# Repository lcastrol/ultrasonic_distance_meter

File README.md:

# ultrasonic_distance_meter
An ultrasonic distance meter 

============
Dependencies
============

Install GCC for AVR and libraries
```
$ sudo apt-get install gcc-avr binutils-avr avr-libc avrdude
```
GDB for AVR
```
$ sudo apt-get install gdb-avr
```

Install Eclipse and the eclipse C development toolkit

```
apt-get install eclipse eclipse-cdt
```

Install eclipse avr plugin

Go to the Software installation dialog (Help > Install New Software...)

Then enter the updatesite URL http://avr-eclipse.sourceforge.net/updatesite into the "Work with:" field. Select the AVR Eclipse Plugin from the list, hit "Next>" and follow the instructions on the next pages.

AVREclipseInstallUpdatesiteScreenshot.png

===================
Configure Eclipse
===================

Go over Window > Preferences

Click on AVR > AVRDude tab
Click on Add button

Choose Programmer Hardware = Atmel AVR ISP

===================
Usage
===================

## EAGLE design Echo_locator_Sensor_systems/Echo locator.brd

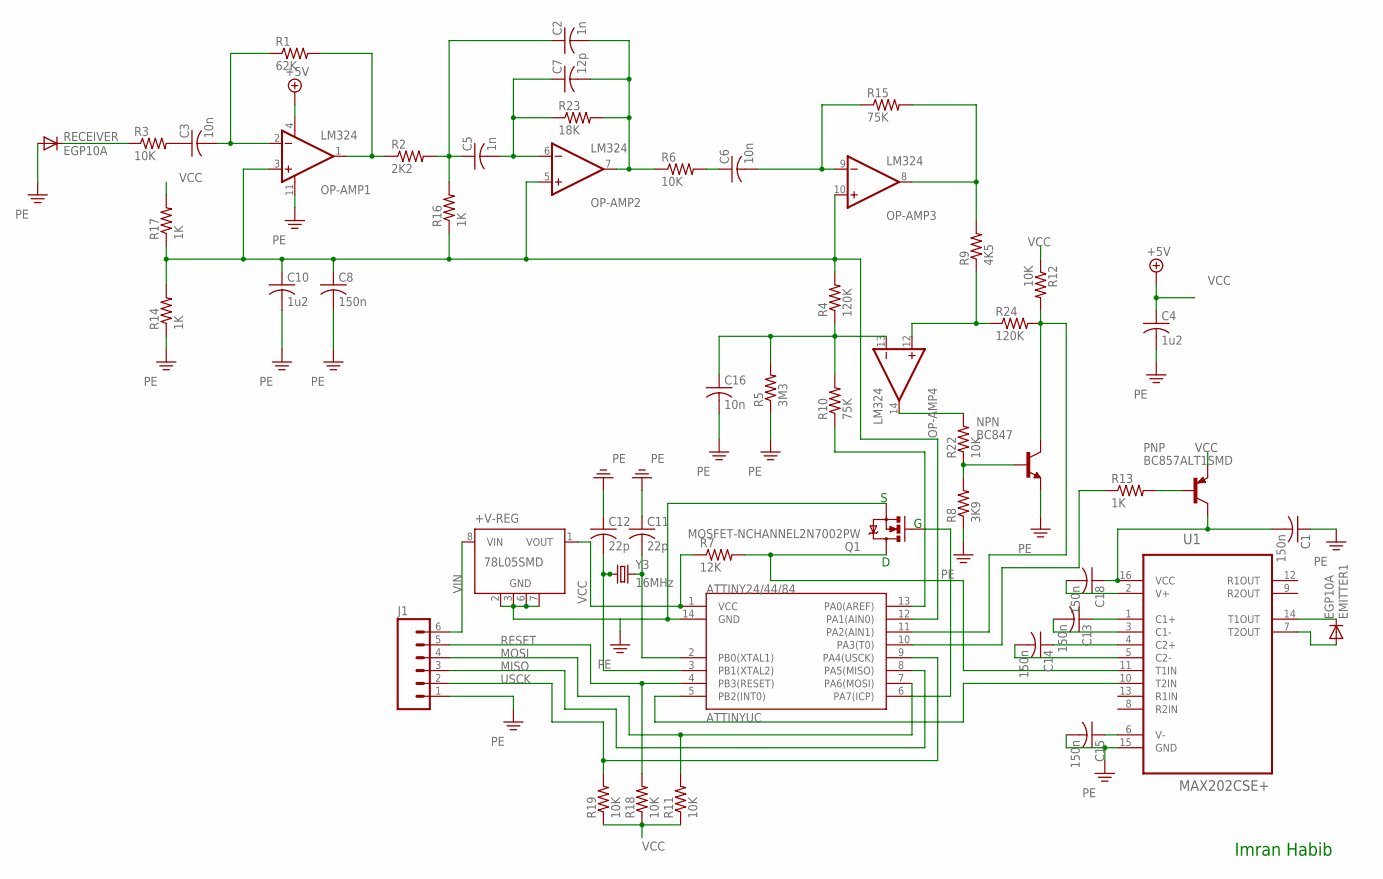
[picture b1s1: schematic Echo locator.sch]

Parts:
+V-REG: 78L05SMD; SO08
ATTINYUC: ATTINY24; SOIC-14
C1, C8, C13, C14, C15, C18: 150n; C0805
C2, C5: 1n; C0805
C3, C6, C16: 10n; C0805
C4, C10: 1u2; C0805
C7: 12p; C0805
C11, C12: 22p; C0805
EMITTER1: EGP10A; DO41-10
J1: M06LONGPADS; 1X06_LONGPADS
NPN: BC847; SOT23
OP-AMP: LM324; SOIC-14
PNP: BC857ALT1SMD; SOT23-BEC
Q1: MOSFET-NCHANNEL2N7002PW; SOT323
R1: 62K; M2012
R2: 2K2; M2012
R3, R6, R11, R12, R18, R19, R22: 10K; M2012
R4, R24: 120K; M2012
R5: 3M3; M2012
R7: 12K; M0805
R8: 3K9; M2012
R9: 4K5; M2012
R10, R15: 75K; M2012
R13, R14, R16, R17: 1K; M2012
R23: 18K; M2012
RECEIVER: EGP10A; DO41-10
U1: MAX202CSE+; SOIC127P600X175-16N
Y3: 16MHz; HC49US

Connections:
C1+: C13.1, U1.1 (C1+)
GND: +V-REG.2 (GND), +V-REG.3 (GND), +V-REG.6 (GND), +V-REG.7 (GND), ATTINYUC.14 (GND), C1.1, C4.2, C8.2, C10.2, C11.1, C12.1, C15.2, C16.2, J1.1, NPN.2 (E), OP-AMP.11 (V-), Q1.2 (S), R5.1, R8.1, R14.1, RECEIVER.A, U1.15 (GND)
ICP: ATTINYUC.6 (PA7(ICP)), Q1.1 (G)
MISO: ATTINYUC.8 (PA5(MISO)), J1.3
MOSI: ATTINYUC.7 (PA6(MOSI)), J1.4, R11.2
unnamed: C3.1, R3.2
unnamed: C3.2, OP-AMP.2 (-IN), R1.1
unnamed: C15.1, U1.6 (V-)
unnamed: OP-AMP.1 (OUT), R1.2, R2.1
unnamed: C2.1, C5.1, R2.2, R16.2
unnamed: C5.2, C7.1, OP-AMP.6 (-IN), R23.1
unnamed: C6.1, R6.2
unnamed: C2.2, C7.2, OP-AMP.7 (OUT), R6.1, R23.2
unnamed: C6.2, OP-AMP.9 (-IN), R15.1
unnamed: OP-AMP.8 (OUT), R9.2, R15.2
unnamed: OP-AMP.14 (OUT), R22.2
unnamed: OP-AMP.12 (+IN), R9.1, R24.1
unnamed: NPN.1 (B), R8.2, R22.1
unnamed: C16.1, OP-AMP.13 (-IN), R4.1, R5.2, R10.2
unnamed: PNP.B, R13.2
unnamed: R3.1, RECEIVER.C
unnamed: ATTINYUC.5 (PB2(INT0)), U1.10 (T2IN)
unnamed: Q1.3 (D), R7.2, U1.11 (T1IN)
unnamed: C13.2, U1.3 (C1-)
unnamed: C14.1, U1.4 (C2+)
unnamed: C14.2, U1.5 (C2-)
unnamed: C18.2, U1.2 (V+)
unnamed: EMITTER1.C, U1.14 (T1OUT)
unnamed: EMITTER1.A, U1.7 (T2OUT)
PA0: ATTINYUC.13 (PA0(AREF)), R10.1
PA1: ATTINYUC.12 (PA1(AIN0)), C8.1, C10.1, OP-AMP.3 (+IN), OP-AMP.5 (+IN), OP-AMP.10 (+IN), R4.2, R14.2, R16.1, R17.1
PA2: ATTINYUC.11 (PA2(AIN1)), NPN.3 (C), R12.2, R24.2
PA3: ATTINYUC.10 (PA3(T0)), R13.1
PB0: ATTINYUC.2 (PB0(XTAL1)), C11.2, Y3.2
PB1: ATTINYUC.3 (PB1(XTAL2)), C12.2, Y3.1
RESET: ATTINYUC.4 (PB3(RESET)), J1.5, R18.2
USCK: ATTINYUC.9 (PA4(USCK)), J1.2, R19.2
VCC: +V-REG.1 (VOUT), ATTINYUC.1 (VCC), C4.1, OP-AMP.4 (V+), PNP.E, R7.1, R11.1, R12.1, R17.2, R18.1, R19.1
VIN: +V-REG.8 (VIN), J1.6
WIRE: C1.2, C18.1, PNP.C, U1.16 (VCC)

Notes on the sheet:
Imran Habib

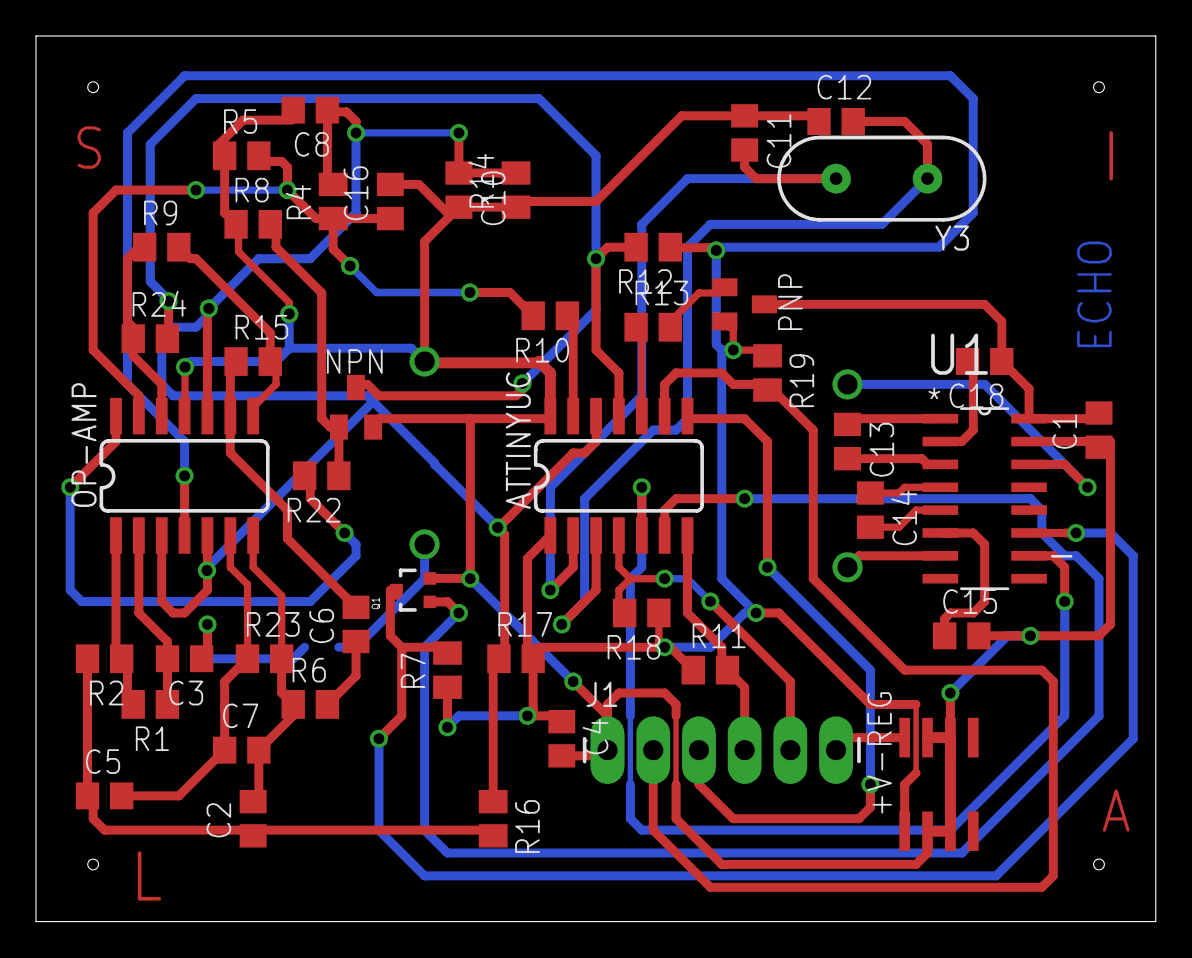
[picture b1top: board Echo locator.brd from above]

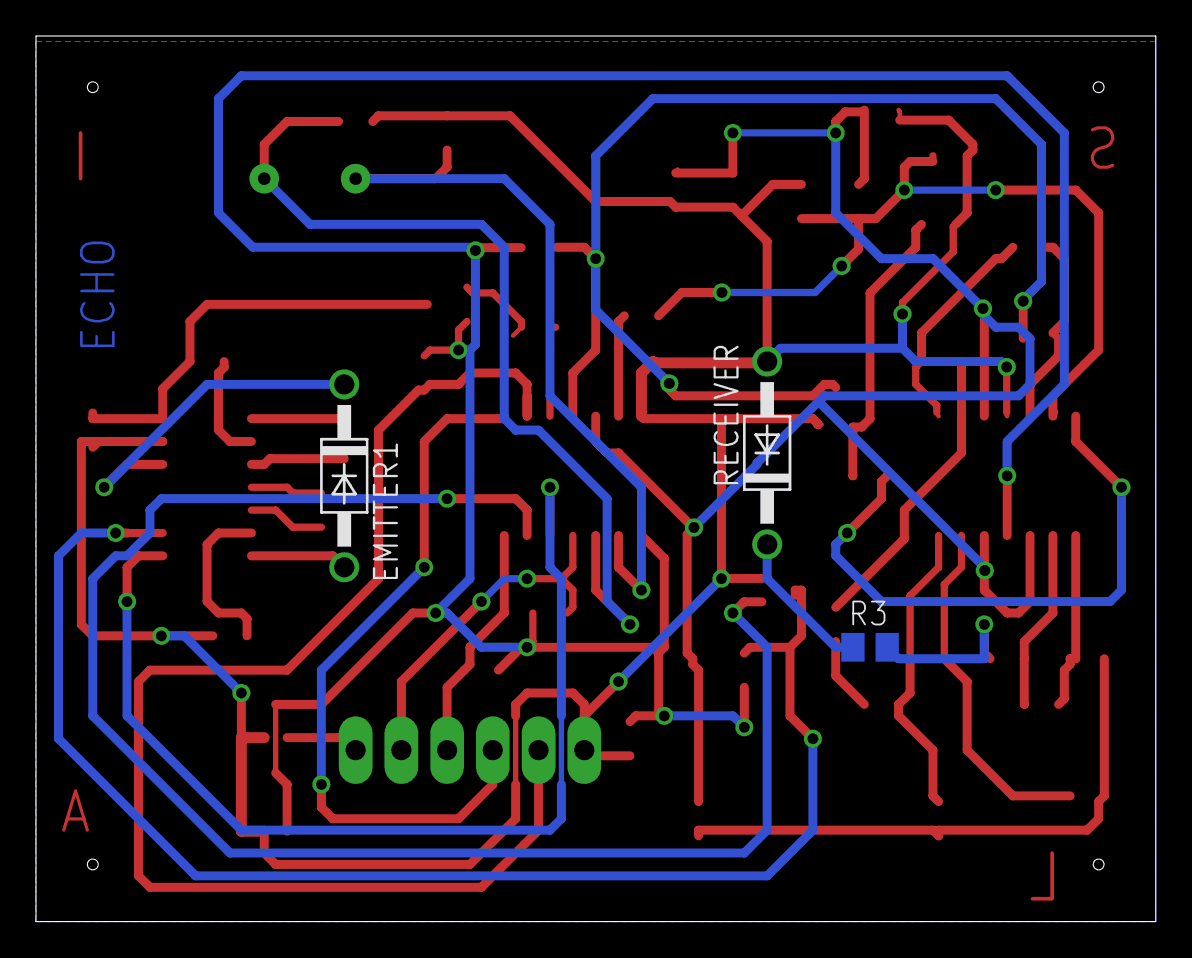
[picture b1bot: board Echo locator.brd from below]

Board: 2 copper layers, 62.2 x 49.2 mm, 49 parts (3 on the bottom side), 40 nets.

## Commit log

2016-11-24 Initial commit to add files
2016-11-24 adding folders and data sheets
2016-11-24 adding more files
2016-11-25 Adding how to install gcc-avr
2016-11-25 playing around with README
2016-11-25 adding firmware files
2016-11-25 Modifying README
2016-11-28 adding prices and quantyties of resistors
2016-11-28 adding order two
2016-11-30 adding attiny setting to the eclipse project
2016-11-30 Modified clock of attiny and BOM
2016-12-02 Start working on the code, timer0 to be tested
2016-12-02 changes in the project files
2016-12-02 adding project files
2016-12-05 adding smart code
2016-12-05 added max202smd to bom and datasheet
2016-12-05 adding files and new code
2016-12-06 Add files via upload
    Schematics and board layout of the echo-locator
2016-12-06 code changes, more new code untested
2016-12-09 Add files via upload
    Schematics, Board layout and Gerber files of the project.
2016-12-11 added cap and resistor values to eagle files
2016-12-11 updated BOM
2016-12-12 New code
2016-12-12 adding new stuff
2016-12-13 more changes in the code
2016-12-13 New files and better code with comparator interrupt
2016-12-15 code major changes
2016-12-19 Updated Board design Files
2016-12-19 New code, many changes, working for both board marginally
2016-12-20 Better code, working with precision of 0,5 cm
2016-12-20 Last working code, Attiny is working for bouncing
2016-12-21 GOOD code
2016-12-21 working code for both boards
2016-12-21 Beta version of full project
2017-01-05 python script measure.py for doing measurements, and report added
2017-01-05 updated report
2017-01-08 Bug fix in the code. Beta code for both boards
2017-01-10 Pushing latest monitor script
2017-01-11 Updated file with parts values

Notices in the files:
parts and their libraries:
SparkFun-Aesthetics: Licensing: Creative Commons ShareAlike 4.0 International - https://creativecommons.org/licenses/by-sa/4.0
